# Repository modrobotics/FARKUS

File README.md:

FARKUS is an open source robotic construction kit for factory automation.
======

At Modular Robotics, we make robot construction kits for kids in our factory in Boulder, CO. Lots of people think this is batshit-crazy; toys are made in China. In order to stay cost-competitive, we do a lot of robotization and automation, but not just by buying a bunch of robot arms. Instead of buying hundred thousand dollar industrial robots and PLCs, we've been making our own industrial robots with 3D printed and laser cut parts and Arduinos.

FARKUS is more than an assembly robot, it's an ecosystem of simple robots that work together. In the same way that our commercial products are made out of lots of tiny robots, the power of FARKUS lies in the modularity and interconnection between various modules that can be reconfigured quickly to support different assembly processes and production lines.

At a basic level, a factory performs a bunch of operations to a bunch of products. The Modular Robotics factory, for instance, uses operations like soldering, ultrasonic welding, programming, testing, and printing to make products like Cubelets and MOSS. FARKUS consists of several parts: movers, to move products through the factory; a collection of modules that perform operations to the products; a control system to manage the ecosystem; and nests to cradle the products as they make their way through a production line.

This repository is pretty rough -- we've dumped files here with only minimal documentation.  We'll update as we make progress and we hope that others will contribute and document.  For now, there are a bunch of Solidworks, Eagle, and code files to peruse along with a few readmes.

More info and media on the wiki at: www.farkus.org

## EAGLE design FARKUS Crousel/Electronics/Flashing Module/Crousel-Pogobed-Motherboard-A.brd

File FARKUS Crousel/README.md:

FARKUS Crousel
======

The Crousel is a mechanism for pogo-testing and/or programming 60 small circuit boards without human intervention.

The hardware folder contains the master solidworks assembly (master.sldasm) which references all other solid parts.

The software folder contains the arduino sketch for the crousel and the firmware for an example flashing module.

The electronics folder contains a fritzing diagram for wiring up a crousel and an example layout for a flashing module.

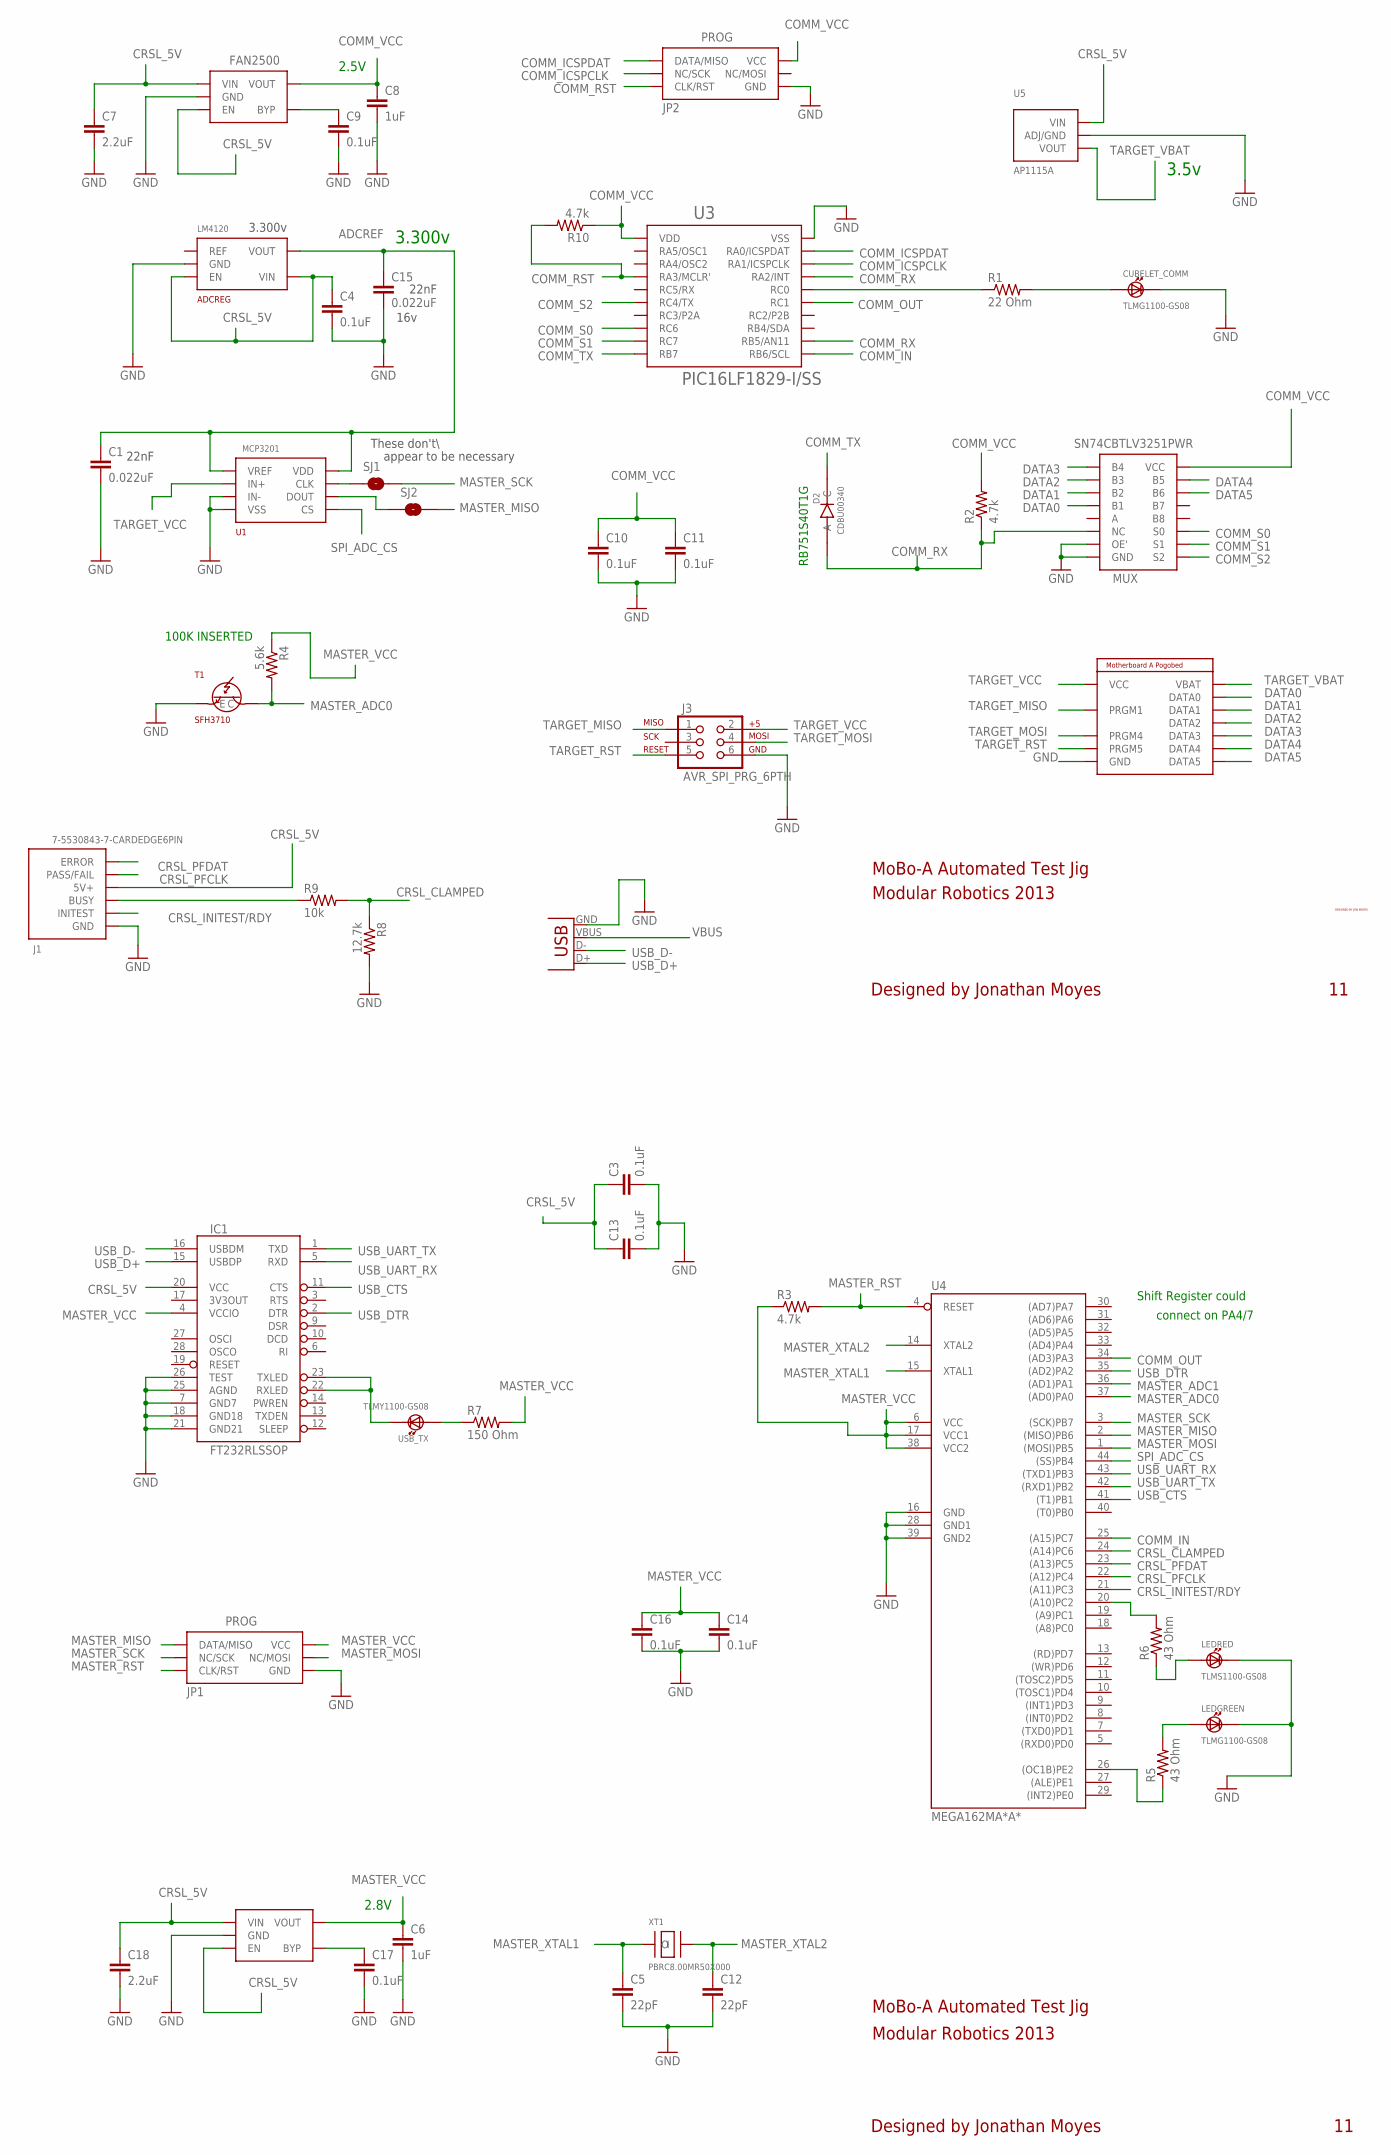
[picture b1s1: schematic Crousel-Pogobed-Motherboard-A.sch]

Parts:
2.8V: FAN2500
ADCREG: LM4120
C1, C15: 0.022uF; 0402-CAP
C3, C4, C9, C10, C11, C13, C14, C16, C17: 0.1uF; 0402-CAP
C5, C12: 22pF; 0402-CAP
C6, C8: 1uF; 0402-CAP
C7, C18: 2.2uF; 0402-CAP
COMMREG: FAN2500
CUBELET_COMM: TLMG1100-GS08; TLM*1100-GS08
D2: CDBU00340
IC1: FT232RLSSOP; SSOP28DB
J1: 7-5530843-7-CARDEDGE6PIN
J2: MOBOA
J3: AVR_SPI_PRG_6PTH; 2X3
JP1, JP2: PROG
LEDGREEN: TLMG1100-GS08; TLM*1100-GS08
LEDRED: TLMS1100-GS08; TLM*1100-GS08
MUX: SN74CBTLV3251PWR
R1: 22 Ohm; 0402-RES
R2, R3, R10: 4.7k; 0402-RES
R4: 5.6k; 0402-RES
R5, R6: 43 Ohm; 0402-RES
R7: 150 Ohm; 0402-RES
R8: 12.7k; 0402-RES
R9: 10k; 0402-RES
SJ1, SJ2: SOLDERJUMPERNO; SJ_2S-NO
T1: SFH3710
U1: MCP3201
U3: PIC16LF1829-I/SS
U4: MEGA162MA*A*; TQFP44
U5: AP1115A; SOT89
U$1: JON_MOYES_SIGNATURE
USB_TX: TLMY1100-GS08; TLM*1100-GS08
X1: USBPTH; USB-B-PTH
XT1: PBRC8.00MR50X000

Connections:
ADCREF: ADCREG.P$5 (VOUT), C1.1, C15.1, U1.P$1 (VREF), U1.P$8 (VDD)
COMM_ICSPCLK: JP2.P$3 (NC/SCK), U3.P$18 (RA1/ICSPCLK)
COMM_ICSPDAT: JP2.P$1 (DATA/MISO), U3.P$19 (RA0/ICSPDAT)
COMM_IN: U3.P$11 (RB6/SCL), U4.25 ((A15)PC7)
COMM_OUT: U3.P$15 (RC1), U4.34 ((AD3)PA3)
COMM_RST: JP2.P$5 (CLK/RST), R10.2, U3.P$4 (RA3/MCLR')
COMM_RX: D2.P$2 (A), MUX.P$6 (NC), R2.1, U3.P$12 (RB5/AN11), U3.P$17 (RA2/INT)
COMM_S0: MUX.P$11 (S0), U3.P$8 (RC6)
COMM_S1: MUX.P$10 (S1), U3.P$9 (RC7)
COMM_S2: MUX.P$9 (S2), U3.P$6 (RC4/TX)
COMM_TX: D2.P$1 (C), U3.P$10 (RB7)
COMM_VCC: C8.1, C10.1, C11.1, COMMREG.P$5 (VOUT), JP2.P$2 (VCC), MUX.P$16 (VCC), R2.2, R10.1, U3.P$1 (VDD)
CRSL_5V: 2.8V.P$1 (VIN), 2.8V.P$3 (EN), ADCREG.P$3 (EN), ADCREG.P$4 (VIN), C3.1, C4.1, C7.1, C13.1, C18.1, COMMREG.P$1 (VIN), COMMREG.P$3 (EN), IC1.20 (VCC), J1.P$4 (5V+), U5.3 (VIN)
CRSL_CLAMPED: R8.1, R9.2, U4.24 ((A14)PC6)
CRSL_INITEST/RDY: J1.P$2 (INITEST), U4.21 ((A11)PC3)
CRSL_PFCLK: J1.P$5 (PASS/FAIL), U4.22 ((A12)PC4)
CRSL_PFDAT: J1.P$6 (ERROR), U4.23 ((A13)PC5)
DATA0: J2.DATA0, MUX.P$4 (B1)
DATA1: J2.DATA1, MUX.P$3 (B2)
DATA2: J2.DATA2, MUX.P$2 (B3)
DATA3: J2.DATA3, MUX.P$1 (B4)
DATA4: J2.DATA4, MUX.P$15 (B5)
DATA5: J2.DATA5, MUX.P$14 (B6)
GND: 2.8V.P$2 (GND), ADCREG.P$2 (GND), C1.2, C3.2, C4.2, C5.2, C6.2, C7.2, C8.2, C9.2, C10.2, C11.2, C12.2, C13.2, C14.2, C15.2, C16.2, C17.2, C18.2, COMMREG.P$2 (GND), CUBELET_COMM.C, IC1.7 (GND7), IC1.18 (GND18), IC1.21 (GND21), IC1.25 (AGND), IC1.26 (TEST), J1.P$3 (GND), J2.PRGM6/GND (GND), J3.6, JP1.P$6 (GND), JP2.P$6 (GND), LEDGREEN.C, LEDRED.C, MUX.P$7 (OE'), MUX.P$8 (GND), R8.2, T1.E, U1.P$3 (IN-), U1.P$4 (VSS), U3.P$20 (VSS), U4.16 (GND), U4.28 (GND1), U4.39 (GND2), U5.2 (ADJ/GND), U5.2@1 (ADJ/GND), X1.GND
LED1: R6.2, U4.20 ((A10)PC2)
MASTER_ADC0: R4.2, T1.C, U4.37 ((AD0)PA0)
MASTER_ADC1: U4.36 ((AD1)PA1)
MASTER_MISO: JP1.P$1 (DATA/MISO), SJ2.2, U4.2 ((MISO)PB6)
MASTER_MOSI: JP1.P$4 (NC/MOSI), U4.1 ((MOSI)PB5)
MASTER_RST: JP1.P$5 (CLK/RST), R3.2, U4.4 (RESET)
MASTER_SCK: JP1.P$3 (NC/SCK), SJ1.2, U4.3 ((SCK)PB7)
MASTER_VCC: 2.8V.P$5 (VOUT), C6.1, C14.1, C16.1, IC1.4 (VCCIO), JP1.P$2 (VCC), R3.1, R4.1, R7.2, U4.6 (VCC), U4.17 (VCC1), U4.38 (VCC2)
MASTER_XTAL1: C5.1, U4.15 (XTAL1), XT1.I
MASTER_XTAL2: C12.1, U4.14 (XTAL2), XT1.O
unnamed: SJ1.1, U1.P$7 (CLK)
unnamed: R1.1, U3.P$16 (RC0)
unnamed: C9.1, COMMREG.P$4 (BYP)
unnamed: CUBELET_COMM.A, R1.2
unnamed: 2.8V.P$4 (BYP), C17.1
unnamed: IC1.22 (RXLED), IC1.23 (TXLED), USB_TX.C
unnamed: R5.1, U4.26 ((OC1B)PE2)
unnamed: R7.1, USB_TX.A
unnamed: LEDGREEN.A, R5.2
unnamed: J1.P$1 (BUSY), R9.1
unnamed: SJ2.1, U1.P$6 (DOUT)
unnamed: LEDRED.A, R6.1
SPI_ADC_CS: U1.P$5 (CS), U4.44 ((SS)PB4)
TARGET_MISO: J2.PRGM1, J3.1
TARGET_MOSI: J2.PRGM4, J3.4
TARGET_RST: J2.PRGM5, J3.5
TARGET_VBAT: J2.VBAT, U5.1 (VOUT)
TARGET_VCC: J2.PRGM2/VCC (VCC), J3.2, U1.P$2 (IN+)
USB_CTS: IC1.11 (CTS), U4.41 ((T1)PB1)
USB_D+: IC1.15 (USBDP), X1.D+
USB_D-: IC1.16 (USBDM), X1.D-
USB_DTR: IC1.2 (DTR), U4.35 ((AD2)PA2)
USB_UART_RX: IC1.5 (RXD), U4.43 ((TXD1)PB3)
USB_UART_TX: IC1.1 (TXD), U4.42 ((RXD1)PB2)
VBUS: X1.VBUS

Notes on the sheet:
16v
3.300v
2.5V
RB751S40T1G
2.8V
Shift Register could
connect on PA4/7
MoBo-A Automated Test Jig
Modular Robotics 2013
Designed by Jonathan Moyes
3.5v
22nF
These don't\
appear to be necessary
100K INSERTED

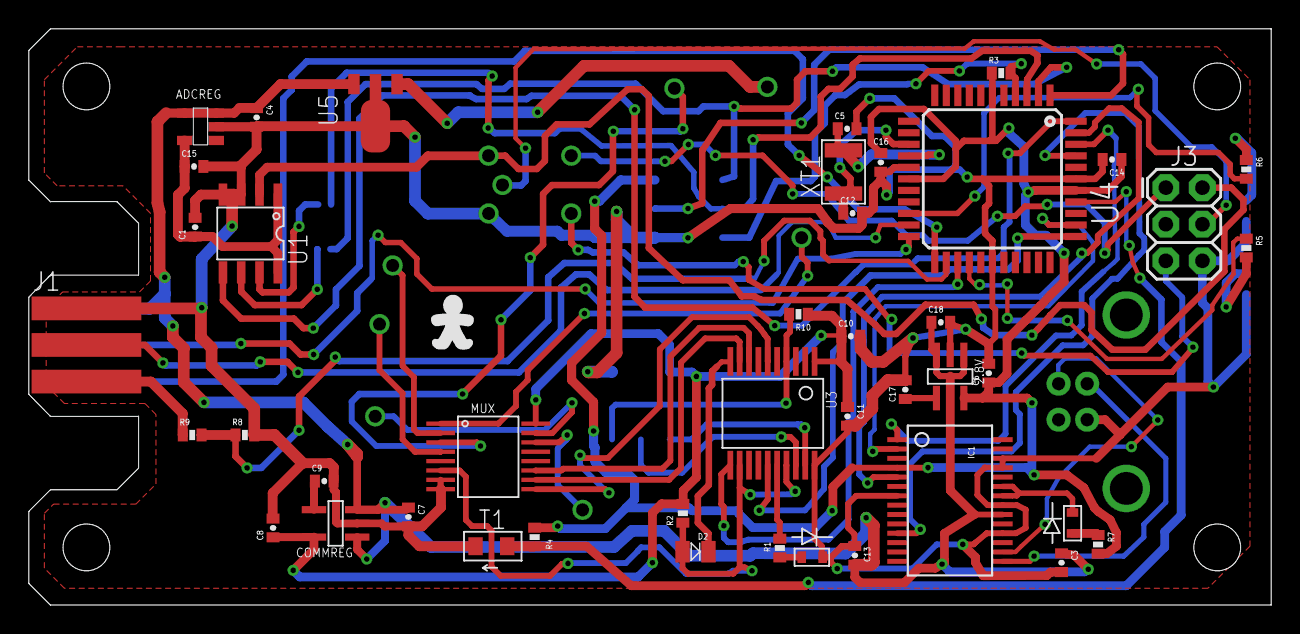
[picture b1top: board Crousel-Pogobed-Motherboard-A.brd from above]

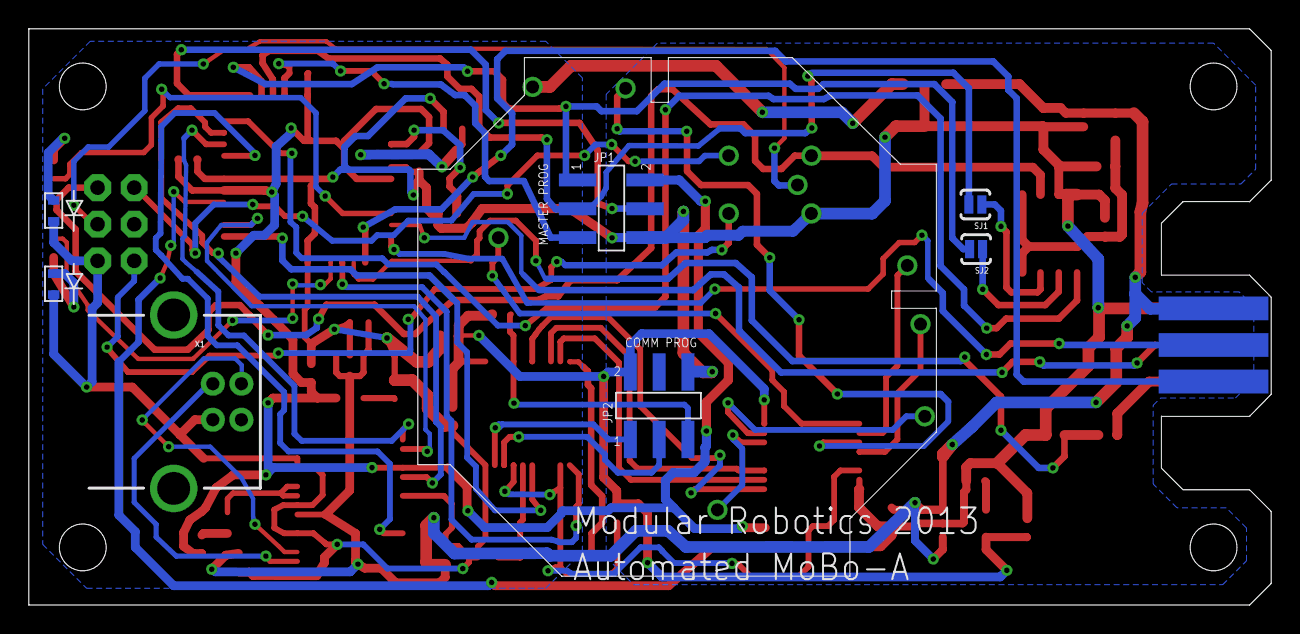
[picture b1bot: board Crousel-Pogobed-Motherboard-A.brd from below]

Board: 2 copper layers, 86.2 x 40.0 mm, 52 parts (8 on the bottom side), 57 nets.

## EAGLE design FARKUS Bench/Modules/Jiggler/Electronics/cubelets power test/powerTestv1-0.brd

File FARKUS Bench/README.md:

FARKUS Bench
======

The FARKUS Bench is an assembly of interconnected modules that work together to complete a set of tasks. We use the Bench to test Cubelets.

The Bench comprises the physical Table, the Conveyance, and Modules, along with the Cubelet Holder (which is a type of FARKUS Nest) and some electrical interfaces.

The Table is the mechanical substrate to which Modules and the Conveyance are fixed. Modules are the units that perform tasks, and the Conveyance is a device that advances workpieces (Cubelets, in our case) through the Modules. The Cubelet Holder is a Nest that has been specifically designed to attach Cubelets to the Conveyance, and the electrical interfaces allow Modules to easily connect up to the Table and communicate with one another.

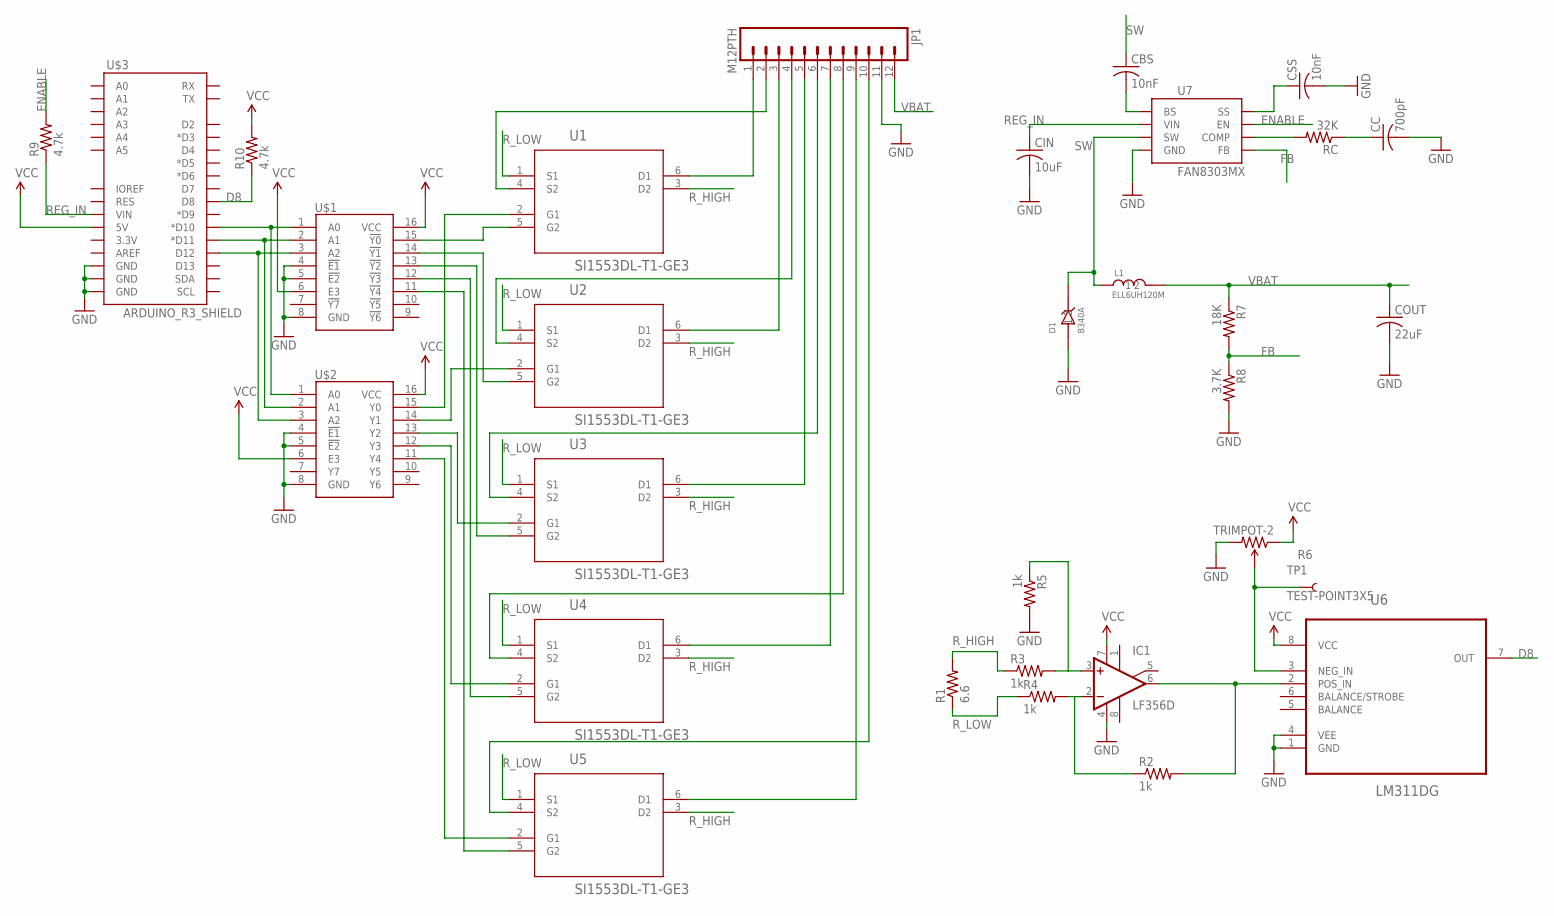
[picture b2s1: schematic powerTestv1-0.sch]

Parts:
CBS: 10nF; C0603
CC: 700pF; C0603
CIN: 10uF; C0603
COUT: 22uF; C0603
CSS: 10nF; C0603
D1: B340A
IC1: LF356D; SO08
JP1: M12PTH; 1X12
L1: ELL6UH120M
R1: 6.6; AXIAL-0.8
R2, R3, R4, R5: 1k; 0603-RES
R6: TRIMPOT-2; TRIMPOT_TC33
R7: 18K; R0603
R8: 3.7K; R0603
R9, R10: 4.7k; R0603
RC: 32K; R0603
TP1: TEST-POINT3X5; PAD.03X.05
U1, U2, U3, U4, U5: SI1553DL-T1-GE3; SOT65P210X110-6N
U6: LM311DG; SOIC127P600X175-8N
U7: FAN8303MX
U$1: 74HC138SO16; SO16
U$2: 74HC238SO16; SO16
U$3: ARDUINO_R3_SHIELD; UNO_R3_SHIELD

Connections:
D8: R10.1, U6.7 (OUT), U$3.D8
ENABLE: R9.2, U7.P$7 (EN)
FB: R7.2, R8.1, U7.P$5 (FB)
GND: CC.2, CIN.2, COUT.2, CSS.2, D1.P$1 (1), IC1.4 (V-), JP1.11, R5.2, R6.3 (CW), R8.2, U6.1 (GND), U6.4 (VEE), U7.P$4 (GND), U$1.4 (!E1), U$1.5 (!E2), U$1.8 (GND), U$2.4 (!E1), U$2.5 (!E2), U$2.8 (GND), U$3.GND@0 (GND), U$3.GND@1 (GND), U$3.GND@2 (GND)
unnamed: U$1.1 (A0), U$2.1 (A0), U$3.D10 (*D10)
unnamed: U$1.2 (A1), U$2.2 (A1), U$3.D11 (*D11)
unnamed: U$1.3 (A2), U$2.3 (A2), U$3.D12
unnamed: U1.5 (G2), U$1.15 (!Y0)
unnamed: U2.5 (G2), U$1.14 (!Y1)
unnamed: U3.5 (G2), U$1.13 (!Y2)
unnamed: U4.5 (G2), U$1.12 (!Y3)
unnamed: U5.5 (G2), U$1.11 (!Y4)
unnamed: U1.2 (G1), U$2.15 (Y0)
unnamed: U2.2 (G1), U$2.14 (Y1)
unnamed: U3.2 (G1), U$2.13 (Y2)
unnamed: U4.2 (G1), U$2.12 (Y3)
unnamed: U5.2 (G1), U$2.11 (Y4)
unnamed: JP1.1, U1.6 (D1)
unnamed: JP1.3, U2.6 (D1)
unnamed: JP1.5, U3.6 (D1)
unnamed: JP1.7, U4.6 (D1)
unnamed: JP1.9, U5.6 (D1)
unnamed: JP1.2, U1.4 (S2)
unnamed: IC1.2 (-IN), R2.1, R4.2
unnamed: IC1.6 (OUT), R2.2, U6.2 (POS_IN)
unnamed: JP1.4, U2.4 (S2)
unnamed: JP1.6, U3.4 (S2)
unnamed: JP1.8, U4.4 (S2)
unnamed: IC1.3 (+IN), R3.2, R5.1
unnamed: R6.2 (WIPER), TP1.P$1, U6.3 (NEG_IN)
unnamed: CSS.1, U7.P$8 (SS)
unnamed: CBS.2, U7.P$1 (BS)
unnamed: RC.2, U7.P$6 (COMP)
unnamed: CC.1, RC.1
unnamed: JP1.10, U5.4 (S2)
REG_IN: CIN.1, R9.1, U7.P$2 (VIN), U$3.VIN
R_HIGH: R1.P$2 (2), R3.1, U1.3 (D2), U2.3 (D2), U3.3 (D2), U4.3 (D2), U5.3 (D2)
R_LOW: R1.P$1 (1), R4.1, U1.1 (S1), U2.1 (S1), U3.1 (S1), U4.1 (S1), U5.1 (S1)
SW: CBS.1, D1.P$2 (2), L1.P$1 (1), U7.P$3 (SW)
VBAT: COUT.1, JP1.12, L1.P$2 (2), R7.1
VCC: IC1.7 (V+), R6.1 (CCW), R10.2, U6.8 (VCC), U$1.6 (E3), U$1.16 (VCC), U$2.6 (E3), U$2.16 (VCC), U$3.5V

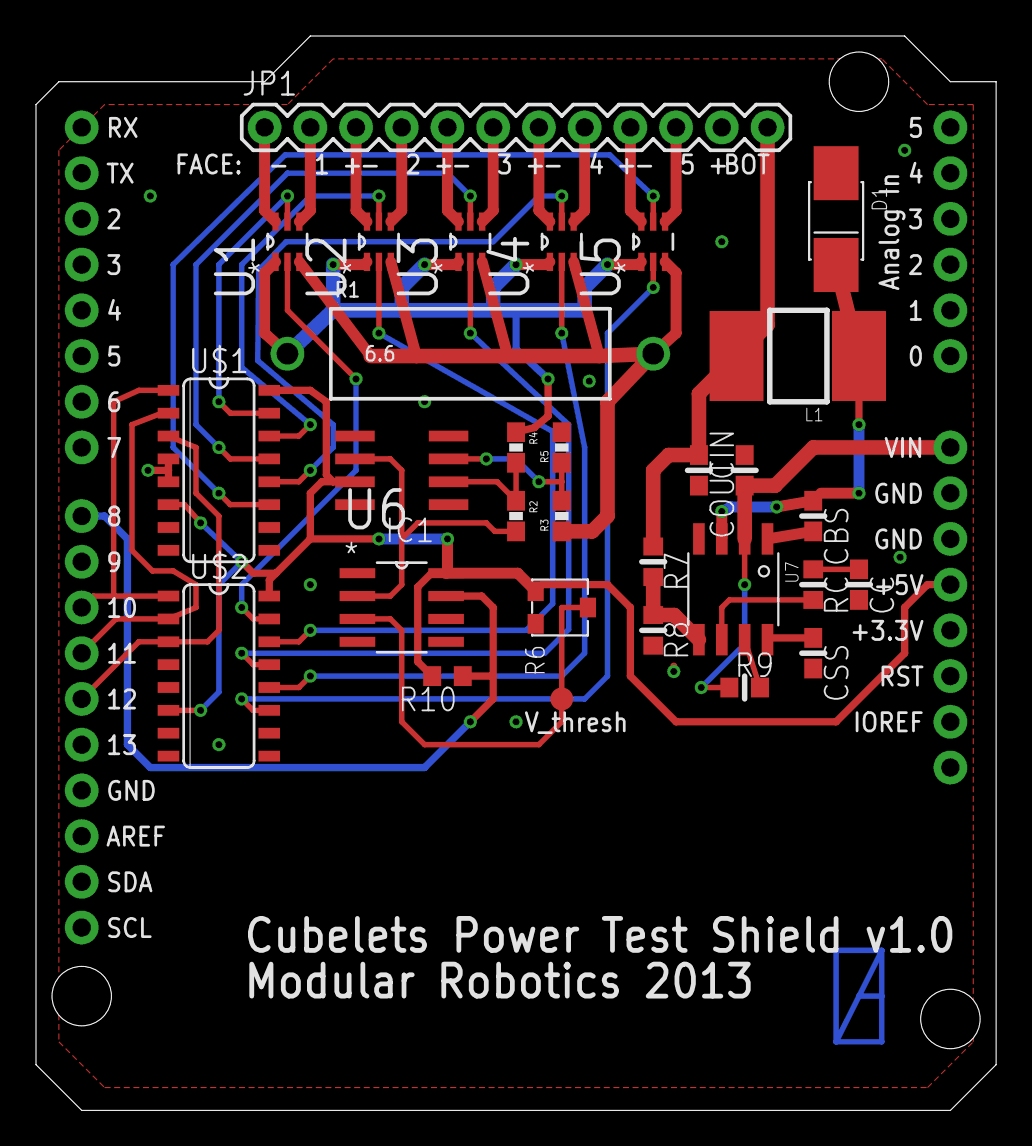
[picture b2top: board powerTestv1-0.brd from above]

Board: 2 copper layers, 53.3 x 59.7 mm, 31 parts (0 on the bottom side), 41 nets.

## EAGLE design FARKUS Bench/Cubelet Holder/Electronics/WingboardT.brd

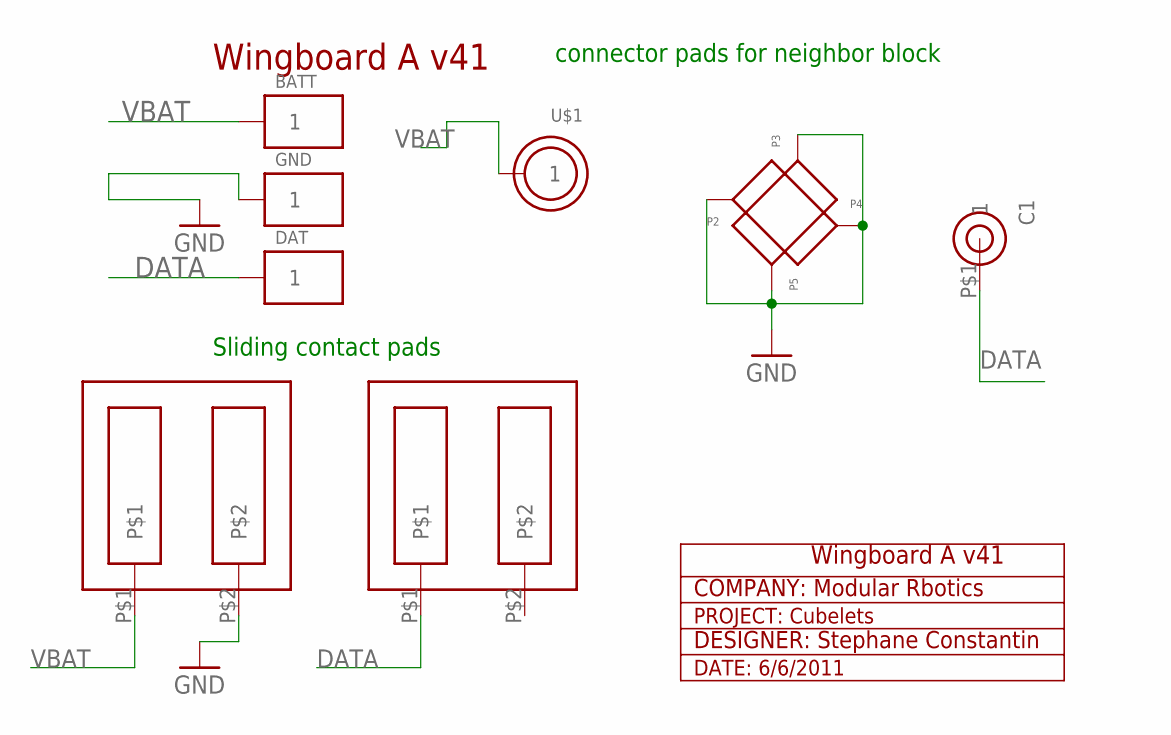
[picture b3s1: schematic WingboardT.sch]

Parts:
BATT: PAD2
C1: COMM_PIN2
DAT: PAD2
GND: PAD2
J1, J2: SLIDING_CONTACT
P2, P3, P4, P5: GND_PAD_WING
U$1: VBAT_CIRCLE

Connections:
DATA: C1.P$1, DAT.P$1, J2.P$1
GND: GND.P$1, J1.P$2, P2.P$1, P3.P$1, P4.P$1, P5.P$1
VBAT: BATT.P$1, J1.P$1, U$1.P$1

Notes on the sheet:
connector pads for neighbor block
COMPANY: Modular Rbotics
DESIGNER: Stephane Constantin
Wingboard A v41
PROJECT: Cubelets
DATE: 6/6/2011
Sliding contact pads

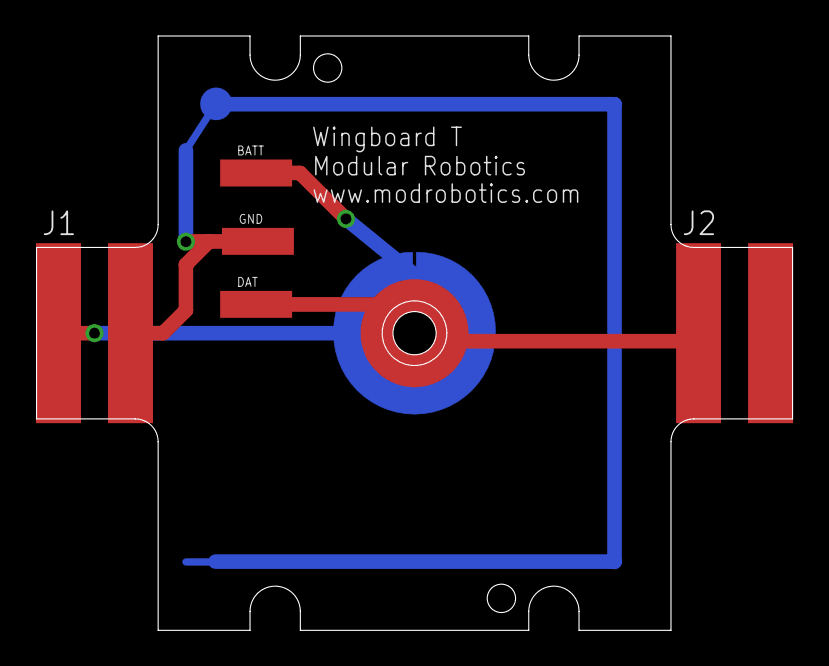
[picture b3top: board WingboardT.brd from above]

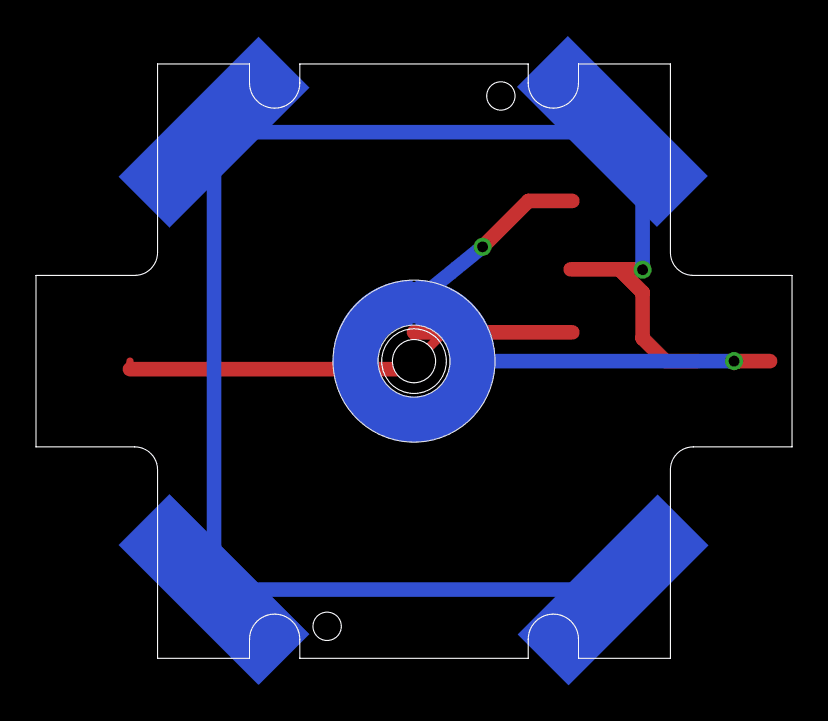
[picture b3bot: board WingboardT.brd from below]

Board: 2 copper layers, 42.0 x 33.0 mm, 11 parts (5 on the bottom side), 3 nets.

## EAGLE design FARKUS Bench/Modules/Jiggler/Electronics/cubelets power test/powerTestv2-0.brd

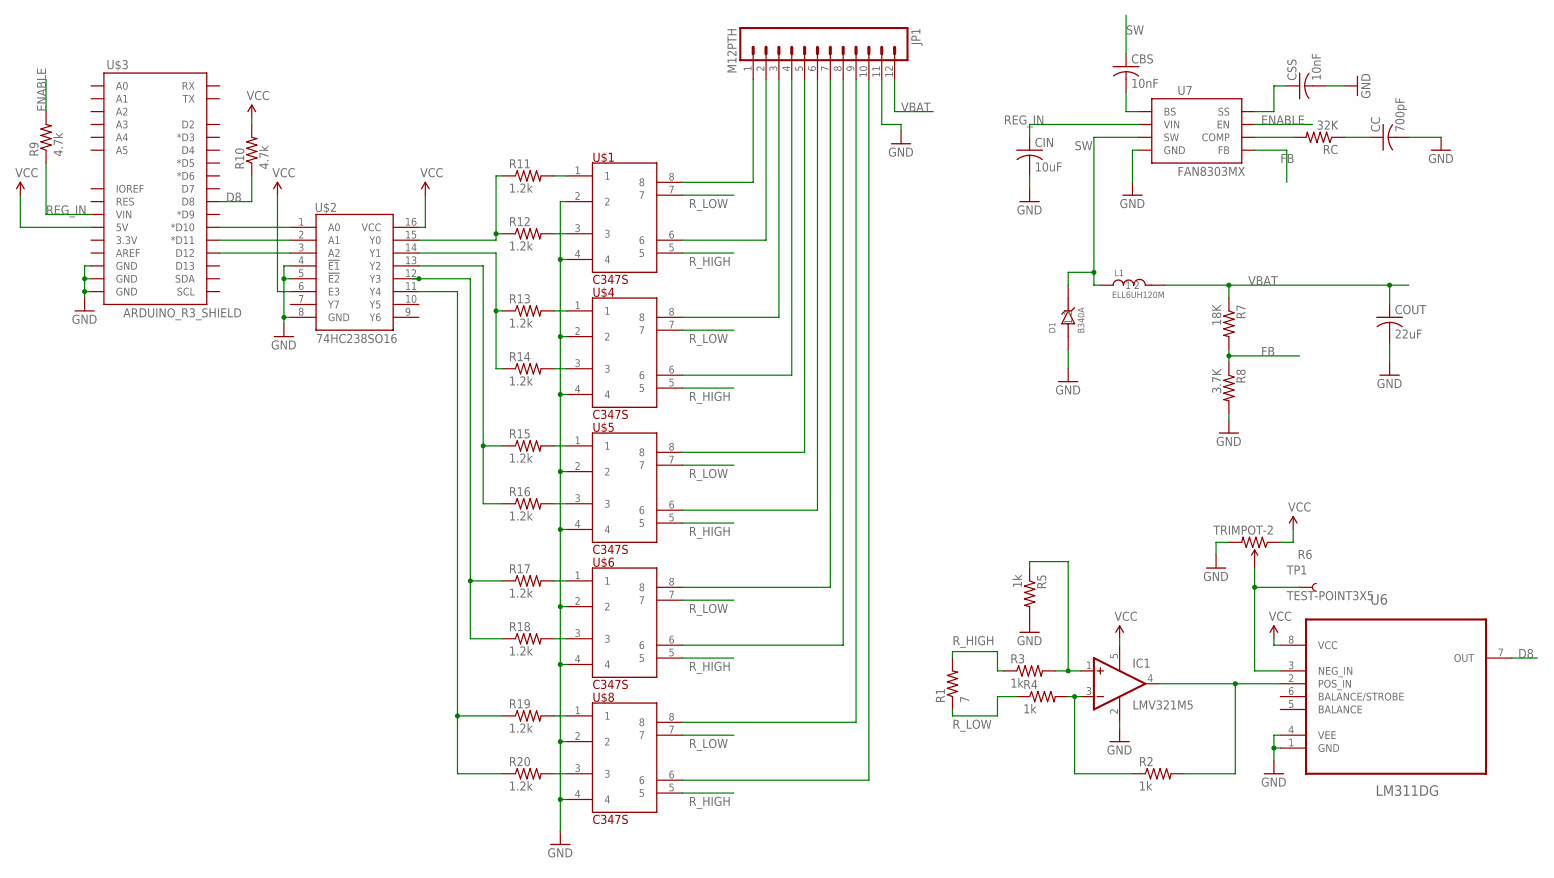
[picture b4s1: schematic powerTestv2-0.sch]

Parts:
CBS: 10nF; C0603
CC: 700pF; C0603
CIN: 10uF; C0603
COUT: 22uF; C0603
CSS: 10nF; C0603
D1: B340A
IC1: LMV321M5; SOT23-5
JP1: M12PTH; 1X12
L1: ELL6UH120M
R1: 7; AXIAL-0.8
R2, R3, R4, R5: 1k; 0603-RES
R6: TRIMPOT-2; TRIMPOT_TC33
R7: 18K; R0603
R8: 3.7K; R0603
R9, R10: 4.7k; R0603
R11, R12, R13, R14, R15, R16, R17, R18, R19, R20: 1.2k; 0603-RES
RC: 32K; R0603
TP1: TEST-POINT3X5; PAD.03X.05
U6: LM311DG; SOIC127P600X175-8N
U7: FAN8303MX
U$1, U$4, U$5, U$6, U$8: C347S; SOP8
U$2: 74HC238SO16; SO16
U$3: ARDUINO_R3_SHIELD; UNO_R3_SHIELD

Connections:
D8: R10.1, U6.7 (OUT), U$3.D8
ENABLE: R9.2, U7.P$7 (EN)
FB: R7.2, R8.1, U7.P$5 (FB)
GND: CC.2, CIN.2, COUT.2, CSS.2, D1.P$1 (1), IC1.2 (V-), JP1.11, R5.2, R6.3 (CW), R8.2, U6.1 (GND), U6.4 (VEE), U7.P$4 (GND), U$1.2, U$1.4, U$2.4 (!E1), U$2.5 (!E2), U$2.8 (GND), U$3.GND@0 (GND), U$3.GND@1 (GND), U$3.GND@2 (GND), U$4.2, U$4.4, U$5.2, U$5.4, U$6.2, U$6.4, U$8.2, U$8.4
unnamed: U$2.1 (A0), U$3.D10 (*D10)
unnamed: U$2.2 (A1), U$3.D11 (*D11)
unnamed: U$2.3 (A2), U$3.D12
unnamed: R12.2, U$1.3
unnamed: R14.2, U$4.3
unnamed: R15.2, U$5.1
unnamed: R16.2, U$5.3
unnamed: R11.2, U$1.1
unnamed: R17.2, U$6.1
unnamed: R18.2, U$6.3
unnamed: JP1.1, U$1.8
unnamed: JP1.2, U$1.6
unnamed: JP1.3, U$4.8
unnamed: JP1.4, U$4.6
unnamed: JP1.5, U$5.8
unnamed: JP1.6, U$5.6
unnamed: IC1.3 (-IN), R2.1, R4.2
unnamed: IC1.4 (OUT), R2.2, U6.2 (POS_IN)
unnamed: JP1.7, U$6.8
unnamed: JP1.8, U$6.6
unnamed: JP1.9, U$8.8
unnamed: IC1.1 (+IN), R3.2, R5.1
unnamed: R6.2 (WIPER), TP1.P$1, U6.3 (NEG_IN)
unnamed: CSS.1, U7.P$8 (SS)
unnamed: CBS.2, U7.P$1 (BS)
unnamed: RC.2, U7.P$6 (COMP)
unnamed: CC.1, RC.1
unnamed: JP1.10, U$8.6
unnamed: R13.2, U$4.1
unnamed: R19.2, U$8.1
unnamed: R20.2, U$8.3
unnamed: R11.1, R12.1, U$2.15 (Y0)
unnamed: R13.1, R14.1, U$2.14 (Y1)
unnamed: R15.1, R16.1, U$2.13 (Y2)
unnamed: R17.1, R18.1, U$2.12 (Y3)
unnamed: R19.1, R20.1, U$2.11 (Y4)
REG_IN: CIN.1, R9.1, U7.P$2 (VIN), U$3.VIN
R_HIGH: R1.P$2 (2), R3.1, U$1.5, U$4.5, U$5.5, U$6.5, U$8.5
R_LOW: R1.P$1 (1), R4.1, U$1.7, U$4.7, U$5.7, U$6.7, U$8.7
SW: CBS.1, D1.P$2 (2), L1.P$1 (1), U7.P$3 (SW)
VBAT: COUT.1, JP1.12, L1.P$2 (2), R7.1
VCC: IC1.5 (V+), R6.1 (CCW), R10.2, U6.8 (VCC), U$2.6 (E3), U$2.16 (VCC), U$3.5V

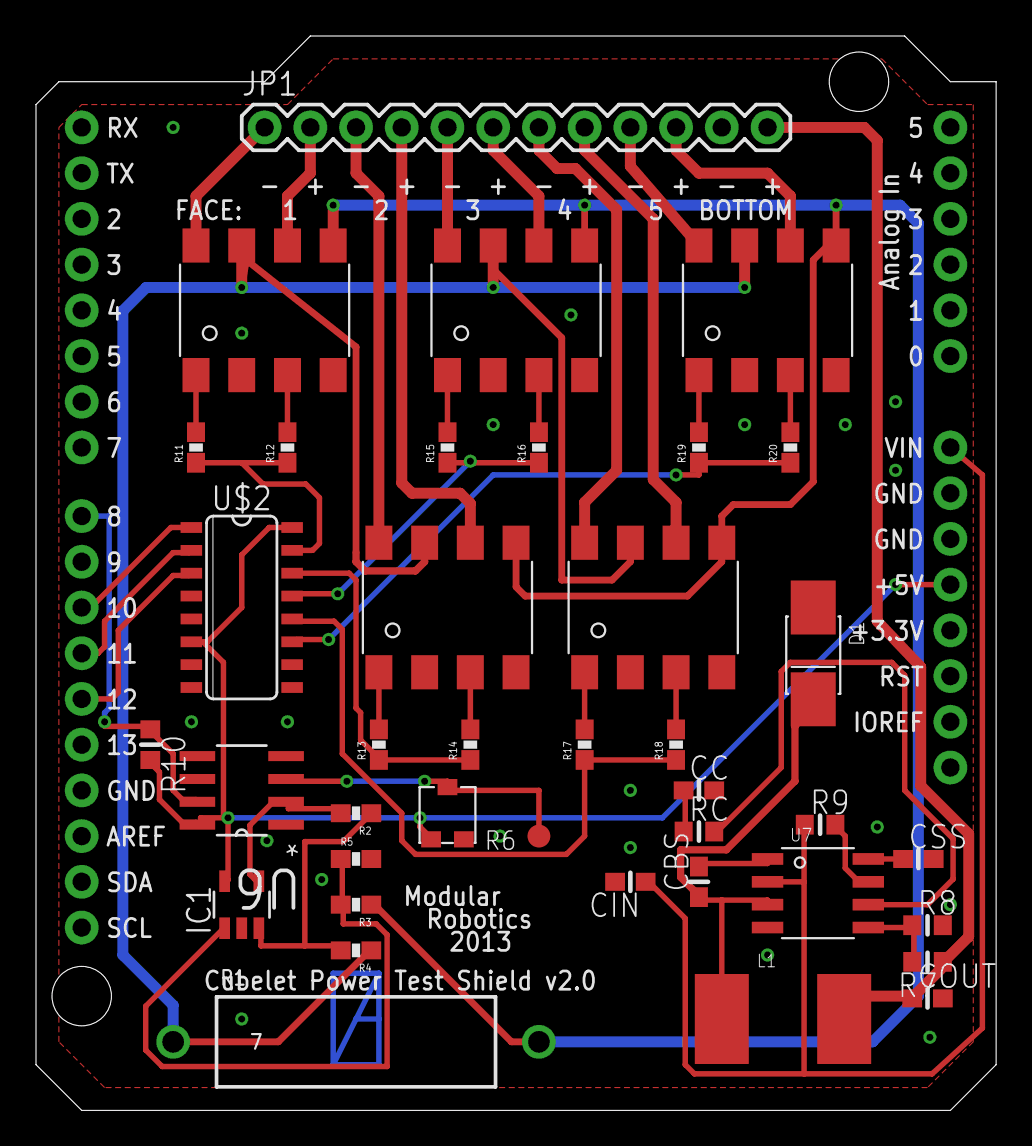
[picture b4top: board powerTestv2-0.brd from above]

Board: 2 copper layers, 53.3 x 59.7 mm, 40 parts (0 on the bottom side), 46 nets.

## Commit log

2013-09-29 Initial import
2013-09-29 Added #! line, fake exe file
2013-09-29 Hooked up module names, position switching. Added skeleton for FarkusTable.Module Shortnames, remove/disconnect before searching again to prevent duplicates, and more
2013-09-29 Now with more readme\!
2013-09-29 Refactor to move singletons into FarkusTable
2013-09-29 Implemented Part, PartType, PartTypeManager
2013-09-29 added part tracking with deque
2013-09-29 tweaks to part tracking to automatically advance, shift, pop, etc
2013-09-29 tweaks to implement conveyance forward+back
2013-09-29 Removed FileInfo template skeleton
2013-09-29 Added icons
2013-09-29 Misc changes that arem't quite right, but I want to MERGE
2013-09-29 Wired up part holder icons, static tests good.
2013-09-29 Readme test
2013-09-29 Readme styling
2013-09-29 Readme updates
2013-09-29 more icons
2013-09-29 Part tracking works! w/ GUI
2013-09-29 mo' betta' BG color to match image
2013-09-29 tweaked window size
2013-09-29 Marking part status works, hookedup to GUI
2013-09-29 Exiting part now log to GUI
2013-09-29 Hooked up Serial Number GUI. Bug fix on exit notifications
2013-09-29 pause button replaced with advance and addpart
2013-09-29 FarkusTest and FarkusTestResult skeletons
2013-09-29 FarkusTestTypes defined. Need to implement searching to enable them to be added to FarkusPartTypes definitions as objects
2013-09-30 Statusbar hooked up. Some bug fixes. Message debug enabled.
2013-09-30 added TODO list.
2013-09-30 implemented dumb module control. Random part s/n, buttons disabled at times
2013-09-30 Reorganized menus, added logic to prevent opening module config if 0 connected
2013-09-30 updated TODO
2013-09-30 Must-have todo list from Farkus meeting
2013-10-02 Snapshot after 8/30 demo. Fixed module IDs
2013-10-02 Added config var, functions to allow skipping intermediate conveyance positions
2013-10-03 double go command bug fixed
2013-10-03 Removed some test code
2013-10-03 Refactored serial response functions - implemented buffering, simple FSM
2013-10-03 Advance fixed, serialworker events hold FarkusModule object
2013-10-04 Some autoadvance/status reporting stuff added
2013-10-04 Initial implementation of simple Clear To Advance
2013-10-14 Pre-surgery commit
    all my local stuff. prototype and running code. the only module running
    prototype code is the 5+1 Communication Prototype.
2013-10-14 removing a submodule for no reason.
2013-10-14 re added the brightness tester prototype after removing it because apparently it was a submodule which is a thing.
2014-02-02 tabpanel gui test
2014-02-02 tabpanel progress...system logger working
2014-02-03 Programmer workers in modules
2014-02-04 Programmer event handling workign
2014-02-05 more improvements
2014-02-07 WORKING!
2014-02-07 Initial release
2014-02-09 Added release firmwares
2014-02-09 Added PAMs
2014-02-09 Added ModuleType records for new beds
2014-02-09 Menu cleanup
2014-02-14 1.0.0 Release of Microphone
2014-08-01 revised folder structure
2014-08-01 add cruzel hardware files
2014-08-04 Initial commit of FARKUS Bench contents
    Includes FARKUS Bench components: Conveyance, Cubelet Holder, Electrical Interfaces, Modules, and Table. Also includes library feature for Cubelets connector in Design Library. Includes most mechanic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
2014-08-04 Create README.md
    added basic readme info
2014-08-04 Added FARKUS Bench README
2014-08-04 renamed crousel folder, moved arduino code to SW
2014-08-04 renamed to FARKUS Crousel
2014-08-04 crousel readme add
2014-08-04 crousel flashing module schematics and code.
2014-08-05 added electronics photos and accompanying readmes to conveyance, comm tester, flashlight-brightness test module
2014-08-05 Update README.md
    minor edit

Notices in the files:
parts and their libraries:
SparkFun-Resistors: Licensing: CC v3.0 Share-Alike You are welcome to use this library for commercial purposes.
